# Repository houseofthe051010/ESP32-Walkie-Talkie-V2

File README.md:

# ESP32 Walkie Talkie V2

ESP32 Walkie Talkie V2 is a custom handheld digital voice-radio board. It combines an ESP32, a dedicated 915 MHz SX1262 radio, digital microphone, Class-D speaker amplifier, battery charging, battery monitoring, USB-C programming, controls, and an external OLED connection on one 45 × 100 mm PCB.

The goal is to build a pair of rechargeable handheld radios that can exchange compressed voice without depending on Wi-Fi, cellular service, or an internet connection. The separate sub-GHz radio provides the long-range link while the ESP32 handles audio capture, compression, controls, display updates, and packet management.

> [!IMPORTANT]
> **Current status: production-candidate PCB design, not a completed physical build.** The PCB has passed ERC/DRC and manufacturing-file validation, but the enclosure and application firmware are not finished and no assembled prototype has been bench-tested yet. See [Hack Club submission status](HACK_CLUB_SUBMISSION.md) before submitting this repository for funding.

## Why this project exists

The project started as an attempt to make a longer-range, customizable alternative to a Wi-Fi-only ESP32 intercom. Designing the complete board also made it possible to choose the controls, audio path, battery monitoring and enclosure geometry instead of stacking several development boards together. A major part of the design process became learning how electrical choices affect real small-run assembly cost, stock availability, mechanical fit and manufacturability.

## What it does

- Captures digital audio with an ICS-43432 I2S microphone.
- Uses the ESP32 to process and eventually compress voice audio.
- Sends packetized audio over an Ai-Thinker Ra-01SH/SX1262 915 MHz radio.
- Drives a 4–8 Ω speaker through a MAX98357A I2S Class-D amplifier.
- Displays channel, battery, and radio state on a hand-wired SSD1306 I2C OLED.
- Provides five buttons, a potentiometer input, status LED, charging LED, and battery-voltage monitoring.
- Charges a single-cell Li-ion/LiPo battery through USB-C.

The intended voice mode is SX1262 GFSK/FSK with a low-rate codec and packet-loss handling. Ordinary LoRa modulation is useful for low-rate telemetry, but it does not provide enough continuous bandwidth for normal real-time voice.

## Hardware

| Subsystem | Part | Purpose |
|---|---|---|
| Controller | ESP32-WROOM-32D-N16 | Audio processing, controls, display and packet handling |
| Long-range radio | Ai-Thinker Ra-01SH / SX1262 | 803–930 MHz radio with I-PEX/U.FL-compatible antenna socket |
| Microphone | ICS-43432 | Bottom-port I2S digital microphone |
| Speaker amplifier | MAX98357A | I2S Class-D differential speaker output |
| Power regulator | TPS63021 | Fixed 3.3 V synchronous buck-boost supply |
| Charger | TP4056 | Approximately 500 mA single-cell Li-ion charging |
| Battery protection | DW01A + FS8205A | Cell overcharge, overdischarge and fault protection |
| USB programming | CH340C | USB-to-UART with automatic boot/reset control |
| Display | External SSD1306 module | Four hand-wired I2C holes: `SDA`, `SCL`, `3V3`, `GND` |

## Design views

| PCB front | PCB back |
|---|---|
|  |  |

The KiCad board is exactly **45.000 × 100.000 mm**, uses **two copper layers**, and includes four 3.2 mm M3 mounting holes. The OLED is mounted above the main PCB on wires or spacers, and the enclosure-mounted 40 mm speaker sits over the upper component region with its Z-clearance checked during enclosure design.

The repository currently contains a PCB STEP export, shown above. A complete enclosure CAD assembly and enclosure source file are still required for a complete Hack Club design submission.

## How the system connects

```text
Li-ion cell -> charger/protection -> power switch -> 3.3 V buck-boost -> ESP32
                                                       |            |
                                                       |            +-> OLED / controls
                                                       +-> microphone / SX1262 radio

Li-ion switched rail -------------------------------------> MAX98357A -> speaker
USB-C -> charging
USB-C -> CH340C -> ESP32 programming UART
Ra-01SH I-PEX socket -> tuned 915 MHz antenna
```

The full circuit is documented by the editable [KiCad schematic](<Schematics/Final Draft/KiCad Project/walkiepcb.kicad_sch>). Off-board wiring and mechanical assembly are described in [ASSEMBLY.md](ASSEMBLY.md).

## Intended use

Once the firmware is implemented, a user will charge each handset through USB-C, attach the correct 915 MHz antenna, turn on the side power switch, select a channel with the controls, and hold the push-to-talk button while speaking. The receiving handset will decode the packets and play the voice through its speaker.

The main switch must be on for USB programming because the CH340C intentionally runs from switched 3.3 V. Charging remains available while the switch is off. Never transmit without an antenna, and use only frequencies and power levels permitted in the operating region.

## Building the project

1. Order the matched Gerber, BOM and corrected CPL files from `Schematics/Final Draft/Manufacturing/`.
2. In the assembler preview, confirm that the ESP32 antenna faces the left board edge and the Ra-01SH matches the supplied render.
3. Inspect and electrically bring up one board using the [first-power-up checklist](<Schematics/Final Draft/KiCad Project/FIRST_POWER_UP_CHECKLIST.md>).
4. Hand-solder the OLED, five buttons, potentiometer, speaker, battery, external LED and power switch according to [ASSEMBLY.md](ASSEMBLY.md).
5. Design and print/machine an enclosure that secures the PCB, speaker, battery, display, antenna cable and controls.
6. Flash and test the application firmware before installing the battery permanently.

The validated release files and exact upload instructions are in [Schematics/Final Draft](<Schematics/Final Draft>). Machine validation for that release reports **ERC 0 errors/0 warnings, DRC 0 violations/0 unconnected pads, and 64/64 BOM/CPL reference parity**.

## Repository map

- [`Schematics/Final Draft`](<Schematics/Final Draft>) — order-candidate KiCad source, Gerbers, BOM, corrected CPL, renders and audit reports
- [`Schematics/KiCad Project`](<Schematics/KiCad Project>) — editable working KiCad project and engineering notes
- [`CAD`](CAD) — PCB STEP export; enclosure CAD is still pending
- [`Firmware`](Firmware) — firmware status and planned architecture
- [`DESIGN_JOURNAL.md`](DESIGN_JOURNAL.md) — dated Hack Club-style build journal
- [`docs/ENGINEERING_HISTORY.md`](docs/ENGINEERING_HISTORY.md) — detailed engineering decisions, mistakes and corrections
- [`BOM.csv`](BOM.csv) — root project-level funding BOM
- [`ASSEMBLY.md`](ASSEMBLY.md) — off-board wiring and build plan
- [`HACK_CLUB_SUBMISSION.md`](HACK_CLUB_SUBMISSION.md) — submission checklist and known blockers

## Project BOM

This budget builds a **pair of handsets** so that the radio link can be tested. Prices are planning estimates in USD and exclude shipping/tax. The PCBA line covers the two-board assembled prototype order; the [engineering BOM](<Schematics/Final Draft/KiCad Project/walkiepcb_bom_full.csv>) lists every installed component and JLC/LCSC number.

| Item | Qty | Est. unit | Est. total | Source / part |
|---|---:|---:|---:|---|
| Two assembled PCBs plus fabrication minimum | 1 lot | $105.00 | $105.00 | [JLCPCB](https://jlcpcb.com/); use the files in `Schematics/Final Draft/Manufacturing/` |
| 0.96-inch SSD1306 I2C OLED | 2 | $8.00 | $16.00 | [Waveshare 0.96-inch OLED (B)](https://www.waveshare.com/0.96inch-oled-b.htm) |
| 40 mm, 4–8 Ω speaker | 2 | $2.00 | $4.00 | [Adafruit 4 Ω 3 W speaker](https://www.adafruit.com/product/3968) or equivalent |
| Protected 1S LiPo battery | 2 | $12.50 | $25.00 | [Adafruit 2000 mAh LiPo](https://www.adafruit.com/product/2011) or enclosure-compatible protected cell |
| 868/915 MHz flexible antenna with I-PEX/U.FL | 2 | $8.00 | $16.00 | Taoglas `FXP75.07.0100A` or equivalent 50 Ω antenna |
| 6 × 6 mm two-pin tactile buttons | 10 | $0.25 | $2.50 | `TL1100F100QG` or footprint-compatible equivalent |
| 10 kΩ linear potentiometer | 2 | $1.00 | $2.00 | Generic panel-mount B10K potentiometer |
| SPST power switch | 2 | $1.00 | $2.00 | Generic panel-mount switch rated above 2 A DC |
| 5 mm external LED | 2 | $0.10 | $0.20 | Generic LED; board includes a 330 Ω resistor |
| Wire, heat-shrink and mounting hardware | 1 lot | $5.00 | $5.00 | Generic hookup materials and M3 hardware |
| Enclosure material | 2 | TBD | TBD | Pending complete enclosure CAD |
| **Estimated subtotal before enclosure/shipping/tax** |  |  | **$177.70** |  |

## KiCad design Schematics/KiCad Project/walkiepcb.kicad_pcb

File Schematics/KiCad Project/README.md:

# Walkie-talkie PCB

This project is a two-layer, 45 × 100 mm handheld voice-radio PCB built around an ESP32-WROOM-32D-N16, an Ai-Thinker Ra-01SH/SX1262 915 MHz radio with I-PEX antenna socket, an ICS-43432 digital microphone, and a MAX98357A Class-D speaker amplifier.

The current design is the **Final Draft (2026-08-27)** of the Revision E WROOM + CH340C + Ra-01SH board. The exact pre-audit Revision E state is preserved in `../Legacy/Revision E pre-final audit 2026-08-27/`. An S3 radio-board variant was discussed but intentionally not built yet.

## Current features

- ESP32-WROOM-32D-N16 with 16 MB flash and onboard 2.4 GHz PCB antenna.
- Ra-01SH / SX1262 803–930 MHz radio, intended for 915 MHz operation, with on-module I-PEX/U.FL-compatible connector.
- CH340C USB-UART with DTR/RTS automatic programming.
- USB-C charging/programming port centered at the bottom.
- TP4056 charger set for approximately 500 mA.
- TPS63021 fixed 3.3 V synchronous buck-boost, allowing regulated operation as a 1S Li-ion cell moves above and below 3.3 V.
- Raw-battery ADC on GPIO34 using a 100 kΩ/100 kΩ divider and 100 nF filter.
- ICS-43432 bottom-port I2S microphone.
- MAX98357A I2S Class-D amplifier powered from `SYS_SW`.
- Four-hole wired interface for a commercial SSD1306 I2C OLED; no soldered bare OLED panel or header model.
- Five hand-soldered buttons: symmetric 2×2 cluster plus isolated BTN5.
- Top-left potentiometer and external LED wiring holes.
- Basic red charging and status LEDs near USB-C.
- Four M3 mounting holes, one in each cleared corner.
- Probe/expansion pads for 3V3, GND, UART TX/RX, EN, GPIO0, LED_STATUS/GPIO2, and GPIO12.
- DW01A + FS8205A cell protection, USB ESD protection, and resettable system fuse retained.
- Final-audit corrections: CH340C uses switched 3V3 logic, and R26 provides the ICS-43432's recommended 100 kΩ SD pull-down.

Real-time voice firmware should use compressed, packetized audio over SX1262 GFSK/FSK. LoRa mode is useful for low-rate, long-range data but is not suitable for ordinary continuous voice bandwidth.

## Design journal

### Initial design

The project began as a compact ESP32 walkie-talkie with USB-C charging/programming, a directly soldered OLED, I2S microphone and speaker amplifier, five controls, Li-ion charging/protection, and a regulated logic rail. The original narrow-board target was about 35 mm.

### Mechanical resize and speaker clarification

The enclosure target changed to approximately 100 mm tall × 45 mm wide. The wider board was used to improve button ergonomics, microphone separation, current routing, USB routing, and RF clearance. A 40 mm speaker occupies the upper enclosure region, but the speaker is mounted above the PCB. Therefore short components and RF/power circuitry are allowed underneath its X/Y projection as long as enclosure Z-clearance is verified. The OLED reference still obeys the hard rule that its top must be at least 47.5 mm below the PCB top; the final reference top is Y = 50.0 mm.

### Power-supply redesign

The AP7361C 3.2 V LDO was removed because a linear regulator would fall out of regulation while a 1S cell still had useful energy. It was replaced with a fixed 3.3 V TPS63021 synchronous buck-boost using the manufacturer's inductor/capacitor arrangement. MAX98357A stayed on the raw switched rail.

### Cost and assembly review

JLC's two-board price was much higher than the sum of retail component prices because setup, stencil, Extended-line feeder fees, and difficult packages dominate very small runs. The bare OLED was also overpriced and sometimes unavailable. The design changed to four bare 2.54 mm holes for a separately purchased SSD1306 I2C OLED module.

Several safety parts were examined as cost-down candidates: the resettable fuse, USB ESD device, DW01A, and FS8205A. They remain in Revision D because they provide fault, transient, overcharge, and overdischarge protection. A deliberately unprotected variant was not released.

### ESP32 and long-range radio decision

An ESP32-S3 with native USB was considered, including a separate S3 version. Economy/standard classification made the small-run price unattractive. The current board instead uses the Economic-compatible ESP32-WROOM-32D-N16 plus CH340C.

The ESP32 no longer needs an external antenna connector. A separate Ra-01SH/SX1262 915 MHz module supplies the long-range link and the I-PEX connector. The radio is near the top edge for coax access. The ESP32 moved downward into the previously empty middle area beneath the elevated OLED, with its PCB antenna facing the left board edge.

### Control and indicator revision

The OLED connector moved upward by 5 mm and was changed to a custom holes-only footprint. The four-button cluster was expanded to 12.5 mm pitch, BTN5 stayed isolated, and the microphone moved directly above BTN5. The POT and external LED holes moved to the top-left. Basic C2286 red LEDs were added for charge and status indication near USB-C.

### Final routing and verification

The board was routed as two layers with 0.40 mm high-current trunks, 0.30 mm 3V3 routing, short package neck-downs, and a B.Cu ground plane. The final difficult connections were the right-edge USB power path and the Class-D negative output. The switch connector pads were normalized to 3.0 mm around 1.5 mm drills so a short 0.20 mm USB edge neck could maintain clearance. The amplifier ground was explicitly carried into the main ground network.

Final machine checks on 2026-08-27:

- ERC: 0 errors, 0 warnings.
- DRC: 0 violations.
- Unconnected pads: 0.
- Board: 45 × 100 mm, two copper layers.

### Revision E mounting, OLED, and expansion update

Four M3 mounting holes were added at the corners, the Ra-01SH moved inward while retaining top-edge coax access, and the high-current wire pads were reduced to 2.6 mm copper around 1.2 mm drills to free mechanical space. The OLED holes were rotated 180° so their physical left-to-right order is `SDA`, `SCL`, `3V3`, `GND`, placing ground on the right. Two nearby DNP probe pads expose the status-LED net (GPIO2) and GPIO12 for optional future hardware. GPIO12 remains a boot-strapping pin and must not be forced to an invalid level during reset.

The Final Draft was machine checked on 2026-08-27: ERC 0 errors and 0 warnings, DRC 0 violations, and 0 unconnected pads.

The hand-soldered connector holes were subsequently labeled on `B.Silkscreen`. The labels identify the potentiometer, external LED, battery, speaker, OLED, and system-switch pads while leaving the component-side layout uncluttered. Copper traces underneath do not interfere because the solder mask separates copper from the silkscreen ink.

Back-side branding was added in the open upper-center region: large italic `Verma Industries` lettering with `ESP32 Walkie Talkie V2` beneath it. The artwork uses ordinary white silkscreen and therefore remains compatible with a black solder-mask order.

The expanded mistakes, failed approaches, fixes, and remaining physical-validation tasks are maintained in the repository-level [`DESIGN_JOURNAL.md`](../../DESIGN_JOURNAL.md). That document is the canonical project history; this file remains the compact hardware overview stored beside the KiCad source.

## Key files

- `walkiepcb.kicad_sch` — current schematic.
- `walkiepcb.kicad_pcb` — current routed PCB.
- `walkiepcb_jlc_bom.csv` — four-column, upload-ready JLC BOM with DNP parts excluded.
- `walkiepcb_bom_full.csv` — engineering BOM with fields for installed and hand-soldered parts.
- `PIN_ASSIGNMENTS.md` — firmware pin map.
- `LAYOUT_NOTES.md` — enclosure coordinates and routing notes.
- `JLC_PART_RESEARCH.md` — part selection and current Economic/stock evidence.
- `JLC_COST_ESTIMATE.md` — small-run cost explanation and planning range.
- `ERC_NOTES.md` — electrical verification record.
- `ORDER_READINESS_REPORT.md` — final pre-production audit, known risks, and uploader checks.
- `ASSEMBLY_ORIENTATION_CHECK.md` — required human verification of U6/U8 and other critical rotations.
- `FIRST_POWER_UP_CHECKLIST.md` — current-limited prototype bring-up sequence.
- `legacy/revision_c_s3_2026-08-24/` — preserved earlier design.

## Before ordering

Upload the Gerber ZIP, BOM, and **corrected JLC CPL** from `../Final Draft/Manufacturing/` together. Never upload the raw KiCad position CSV as the CPL. In JLC's preview, U6's PCB antenna must face the left edge and U8 must match the supplied top render, with its I-PEX connector on the module's board-interior/lower side. Recheck every Extended row for live stock and exact package match, especially the ICS-43432, TPS63021, CH340C, ESP32-WROOM, MAX98357A, and Ra-01SH.

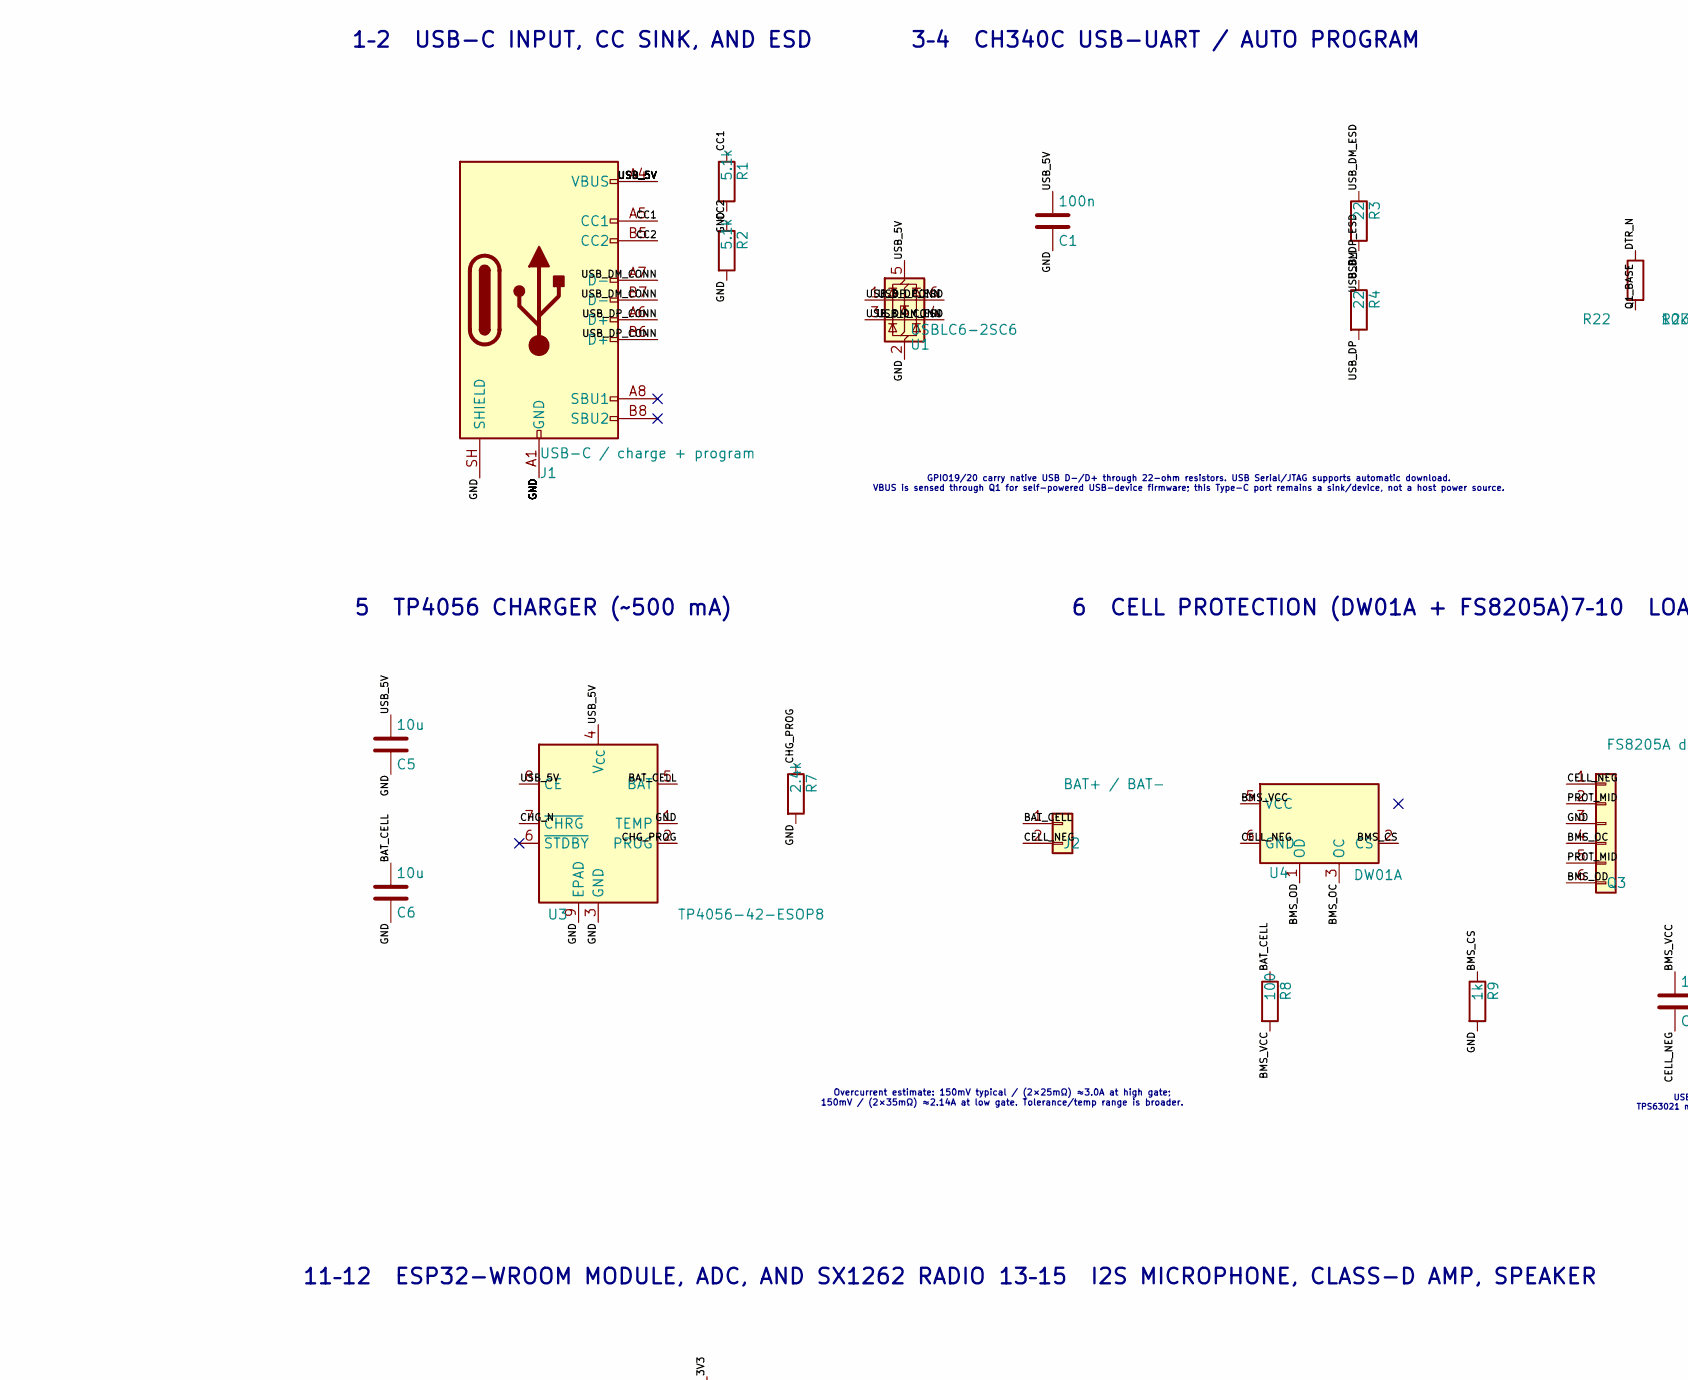
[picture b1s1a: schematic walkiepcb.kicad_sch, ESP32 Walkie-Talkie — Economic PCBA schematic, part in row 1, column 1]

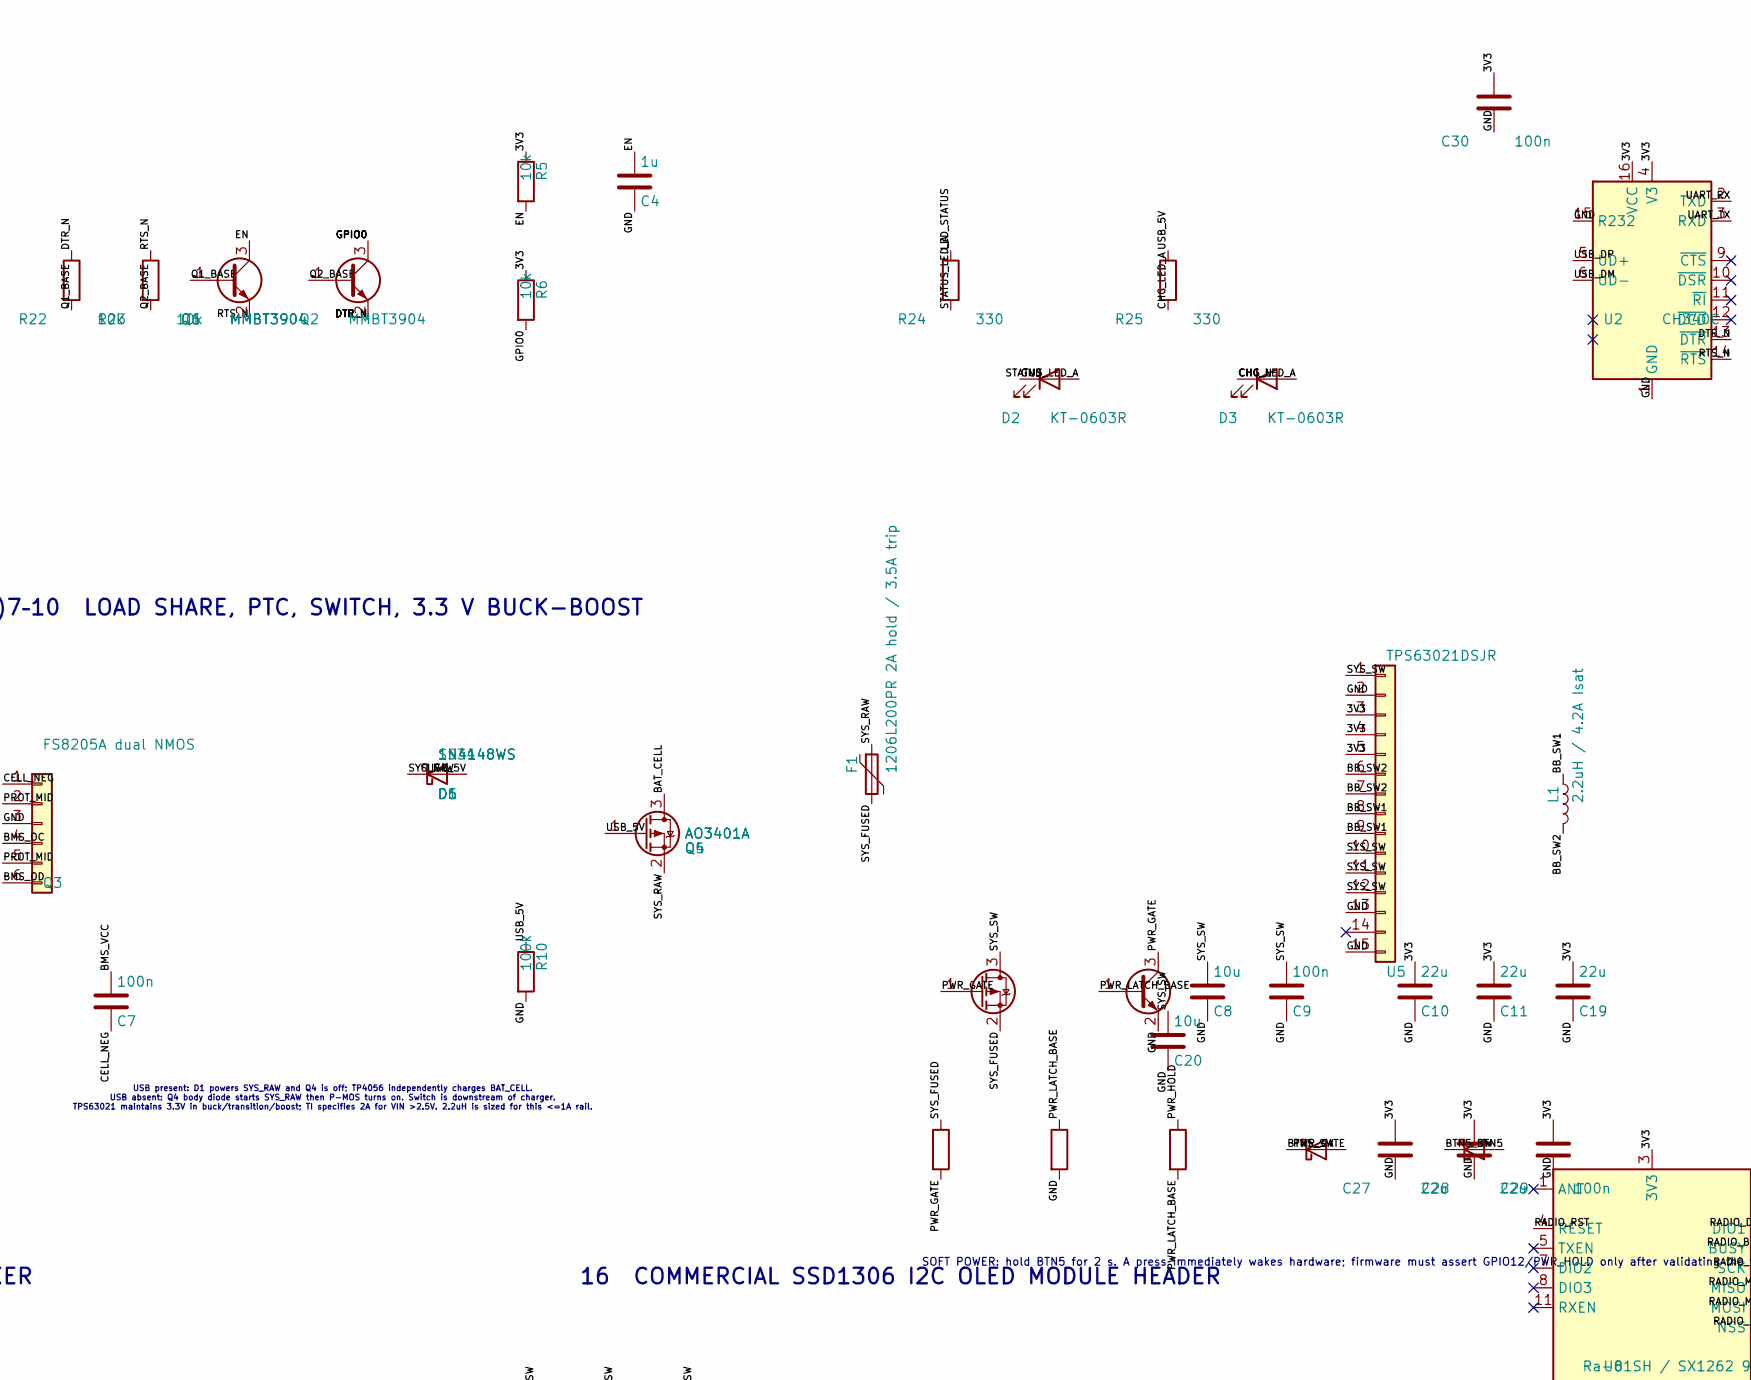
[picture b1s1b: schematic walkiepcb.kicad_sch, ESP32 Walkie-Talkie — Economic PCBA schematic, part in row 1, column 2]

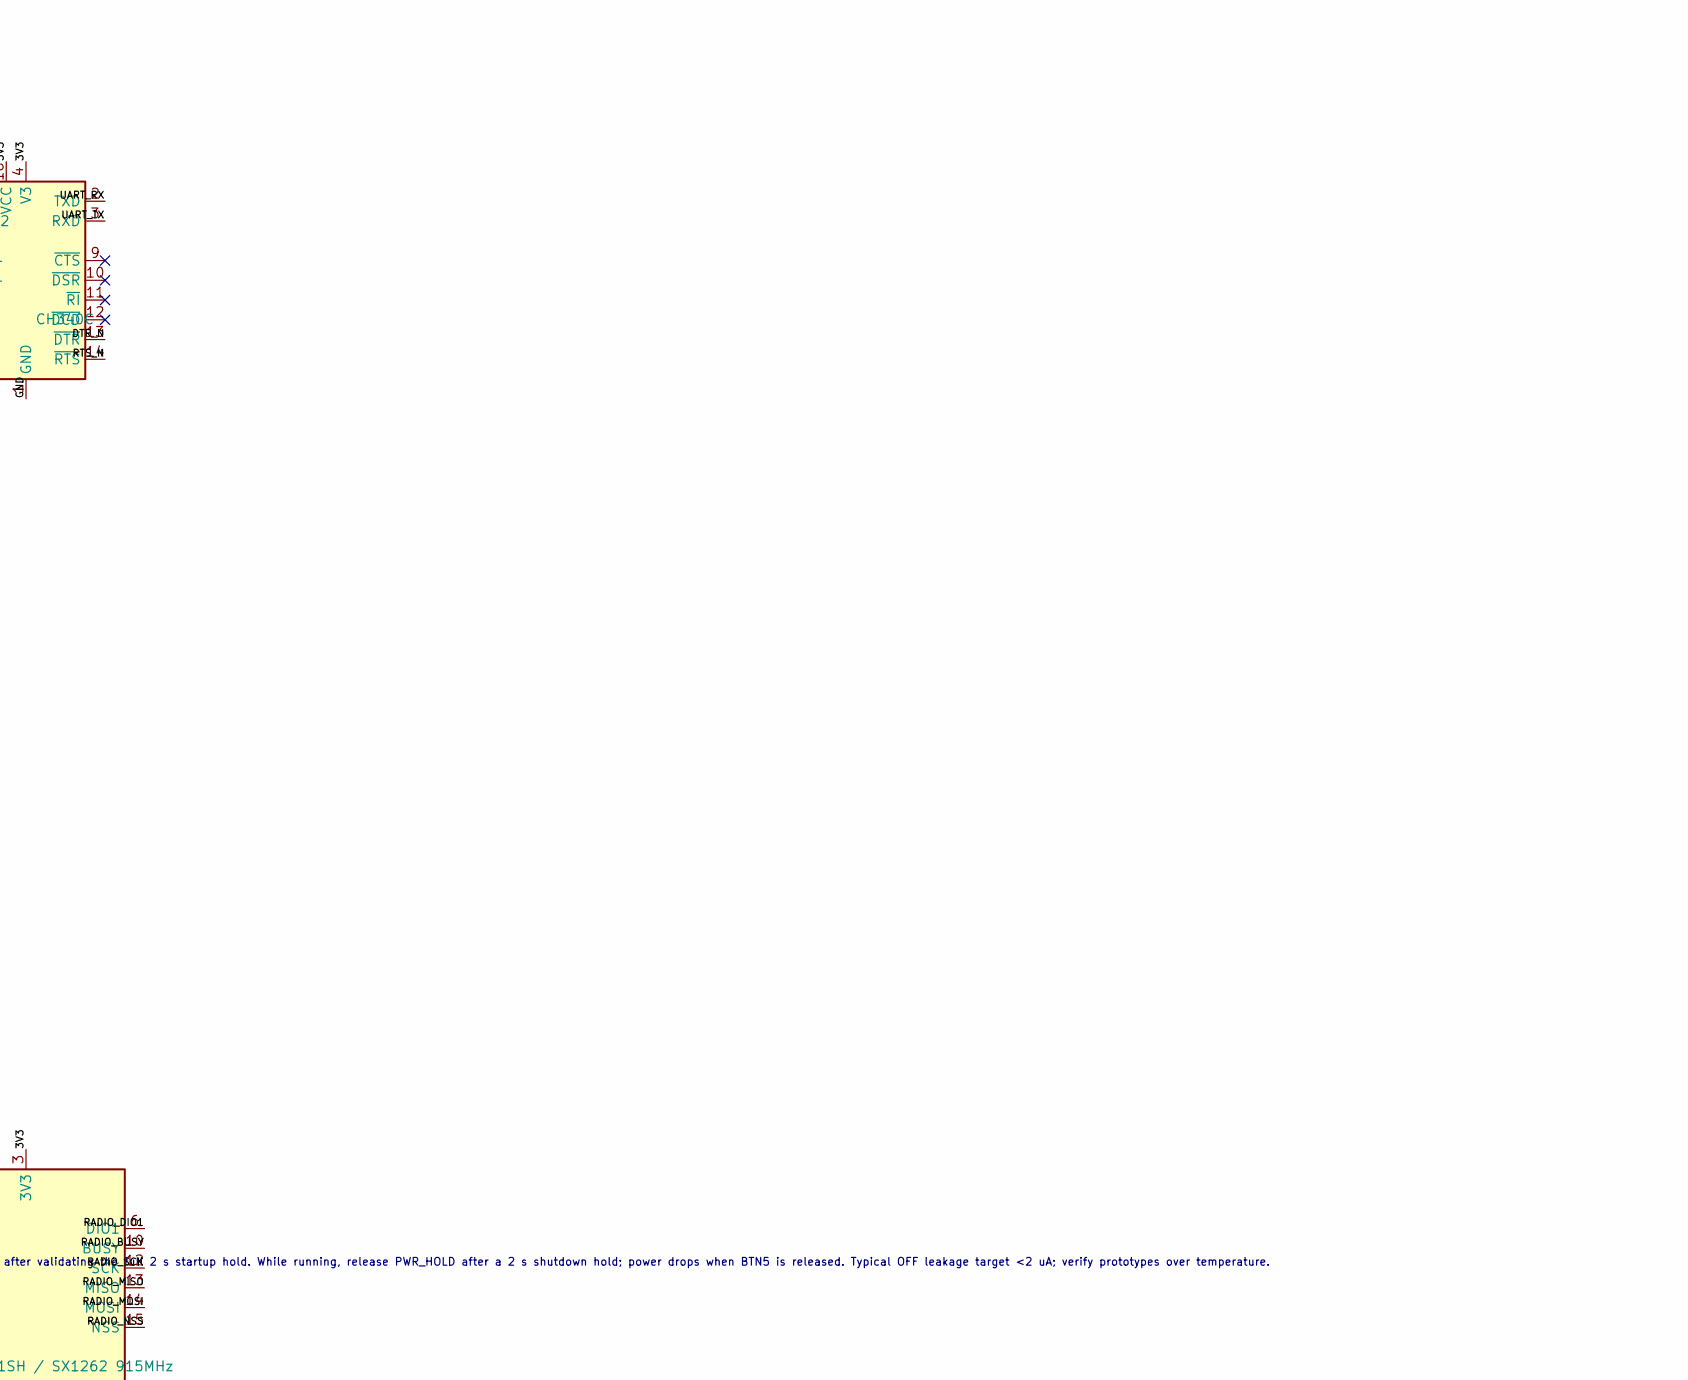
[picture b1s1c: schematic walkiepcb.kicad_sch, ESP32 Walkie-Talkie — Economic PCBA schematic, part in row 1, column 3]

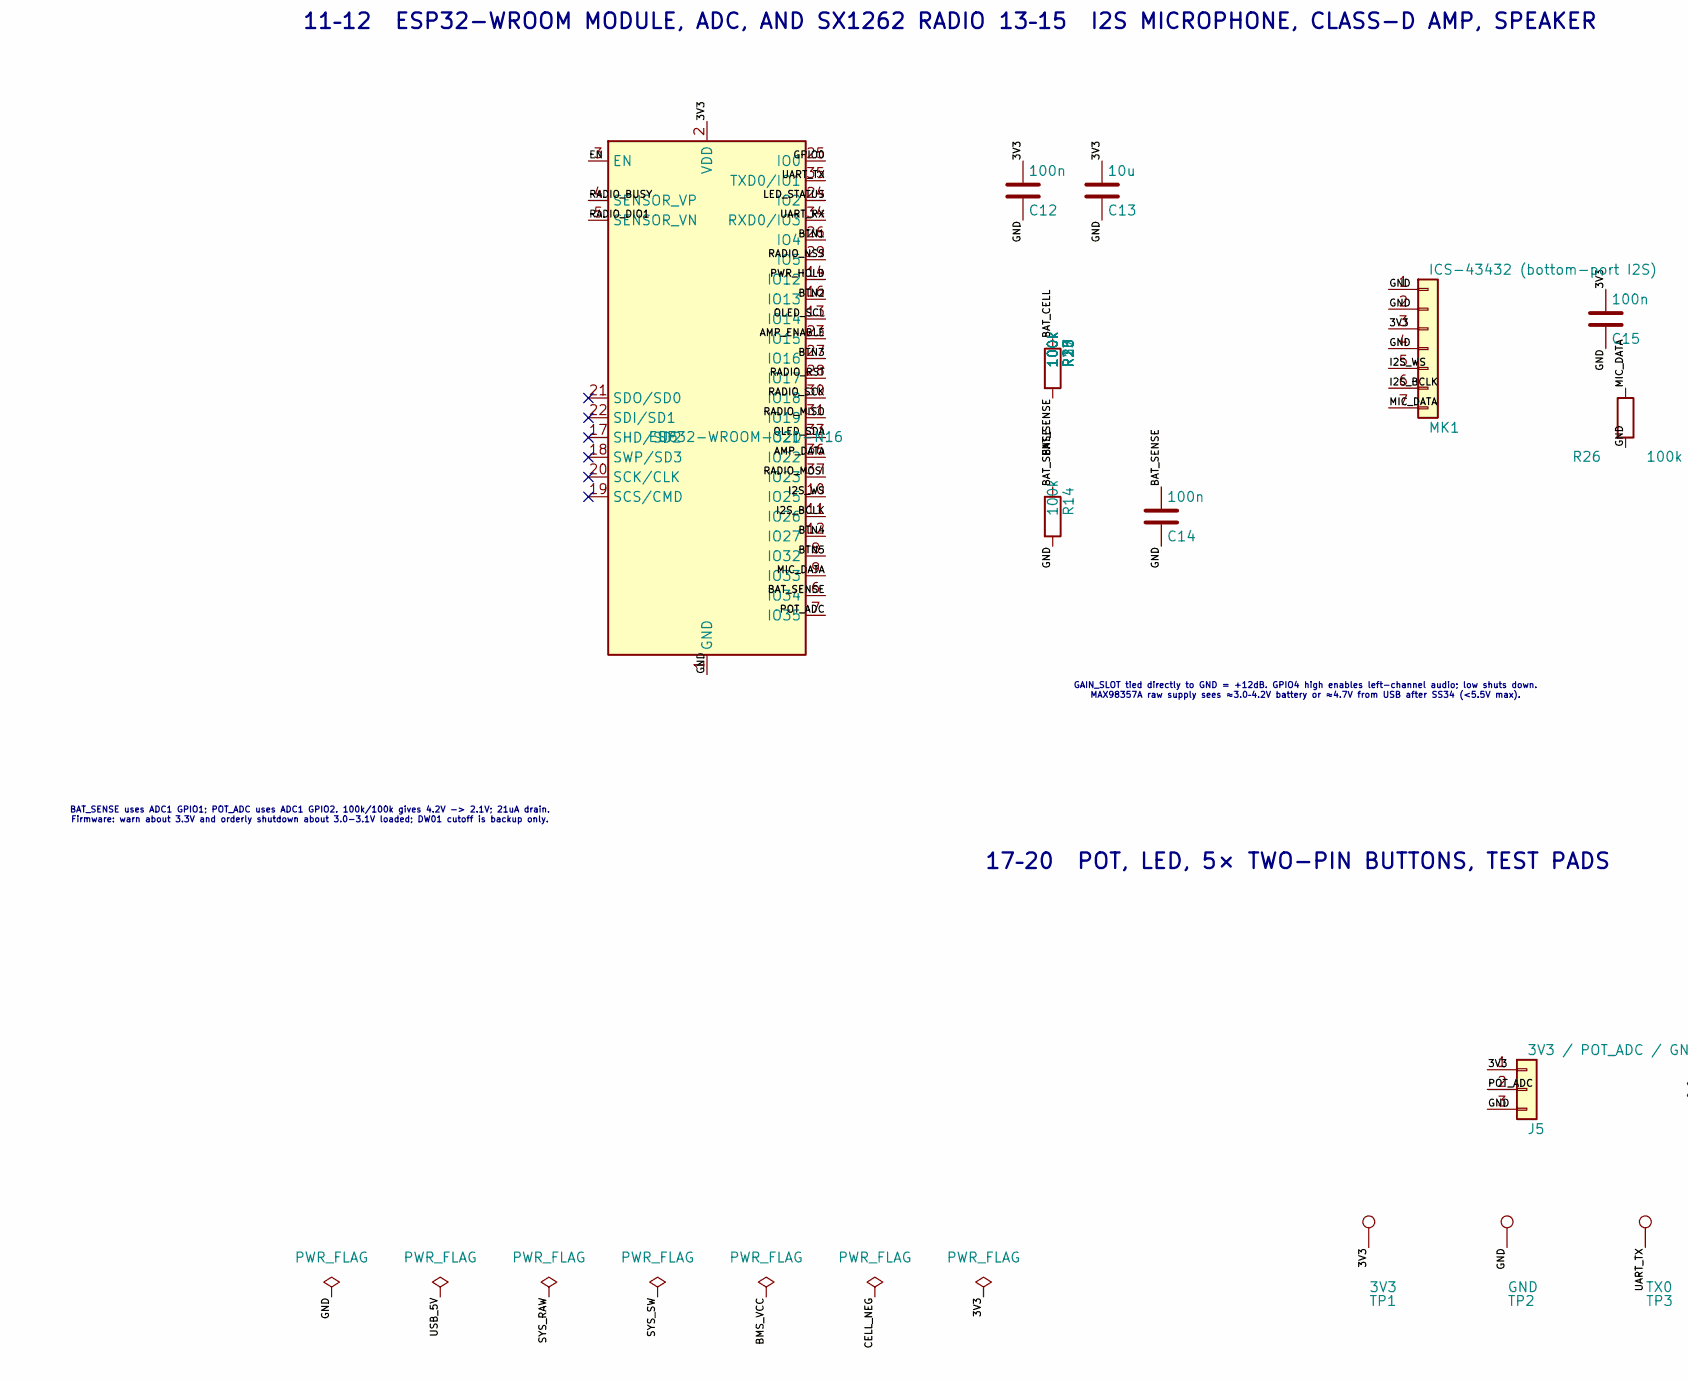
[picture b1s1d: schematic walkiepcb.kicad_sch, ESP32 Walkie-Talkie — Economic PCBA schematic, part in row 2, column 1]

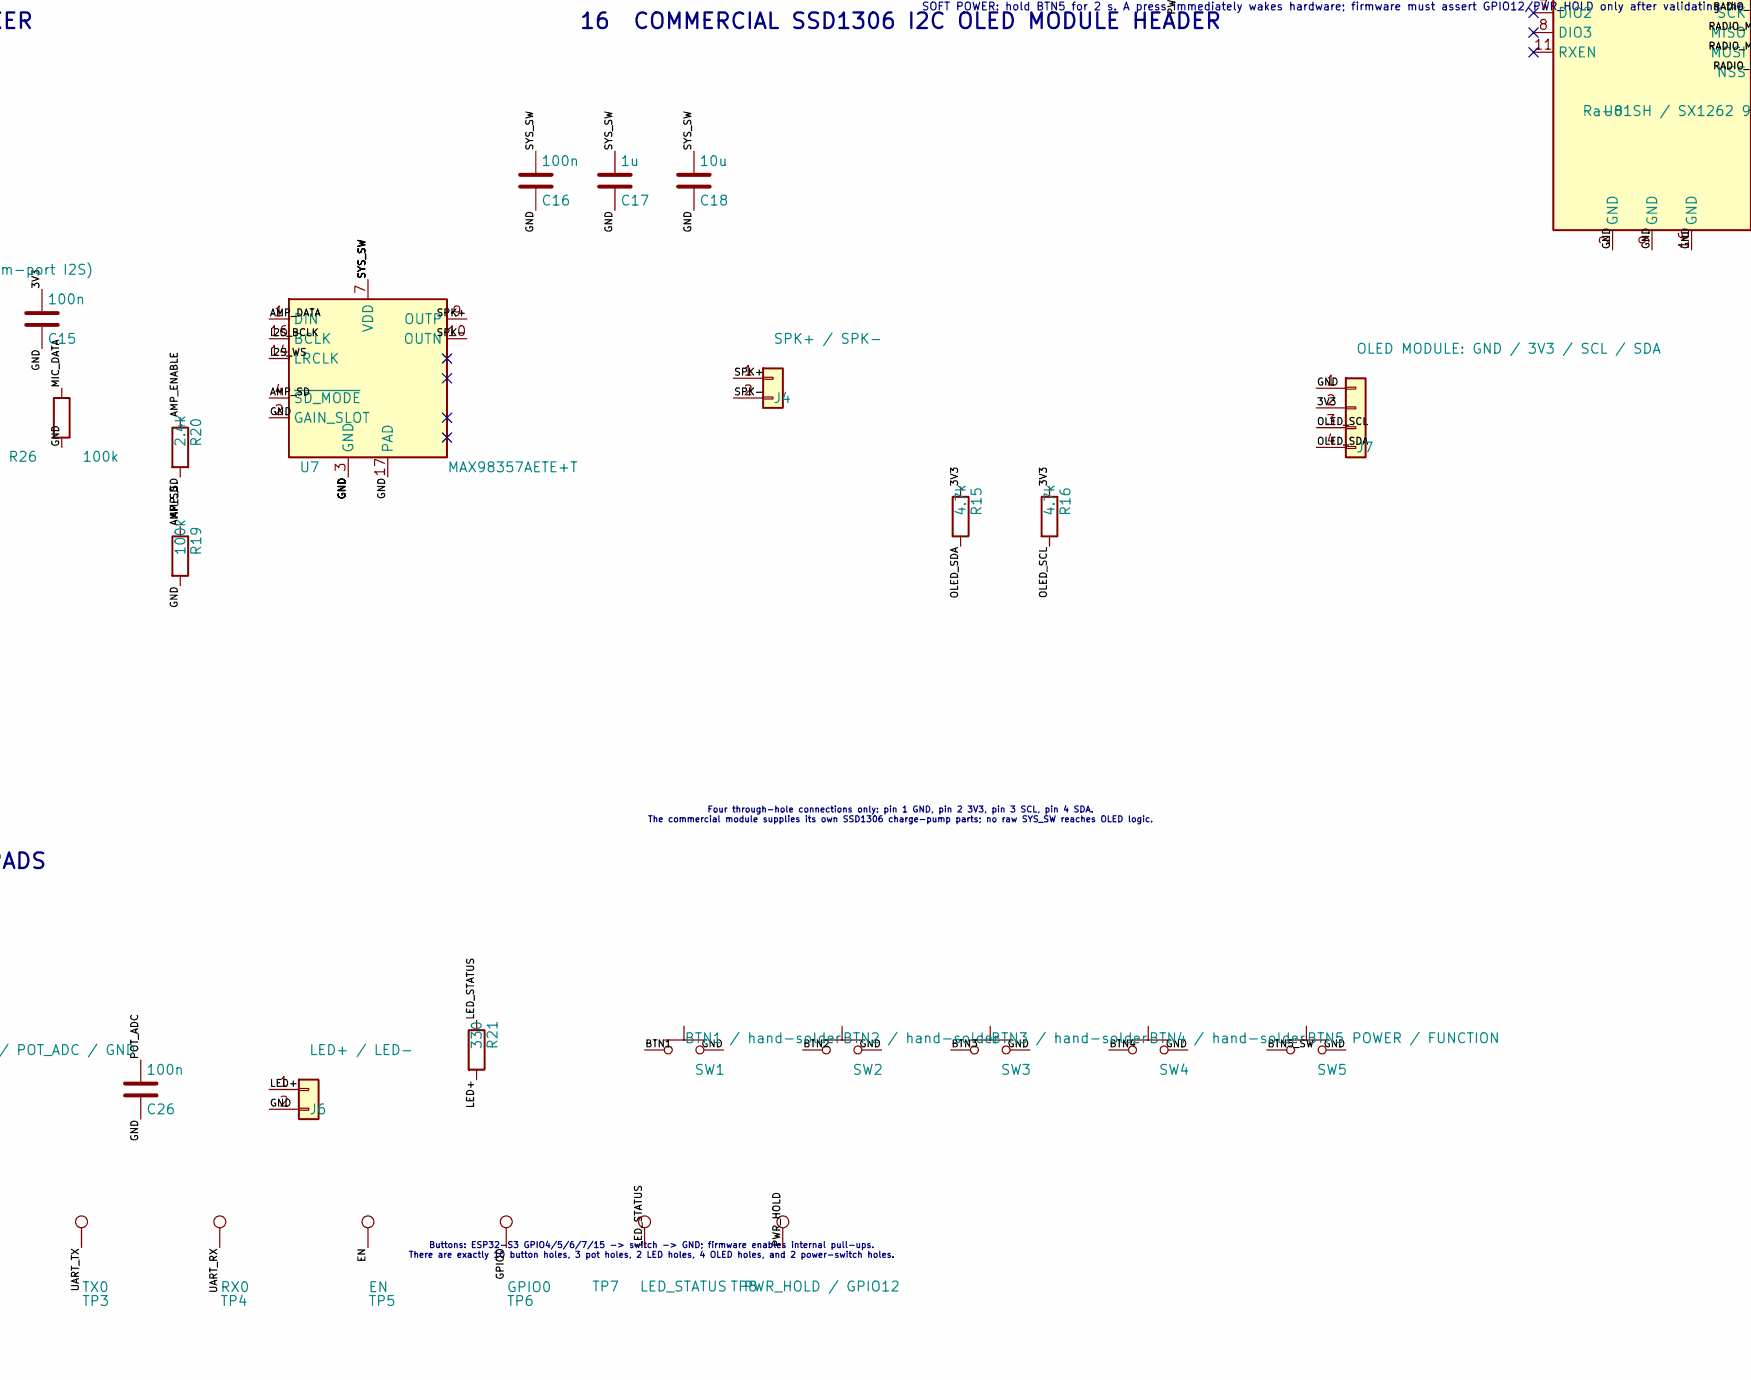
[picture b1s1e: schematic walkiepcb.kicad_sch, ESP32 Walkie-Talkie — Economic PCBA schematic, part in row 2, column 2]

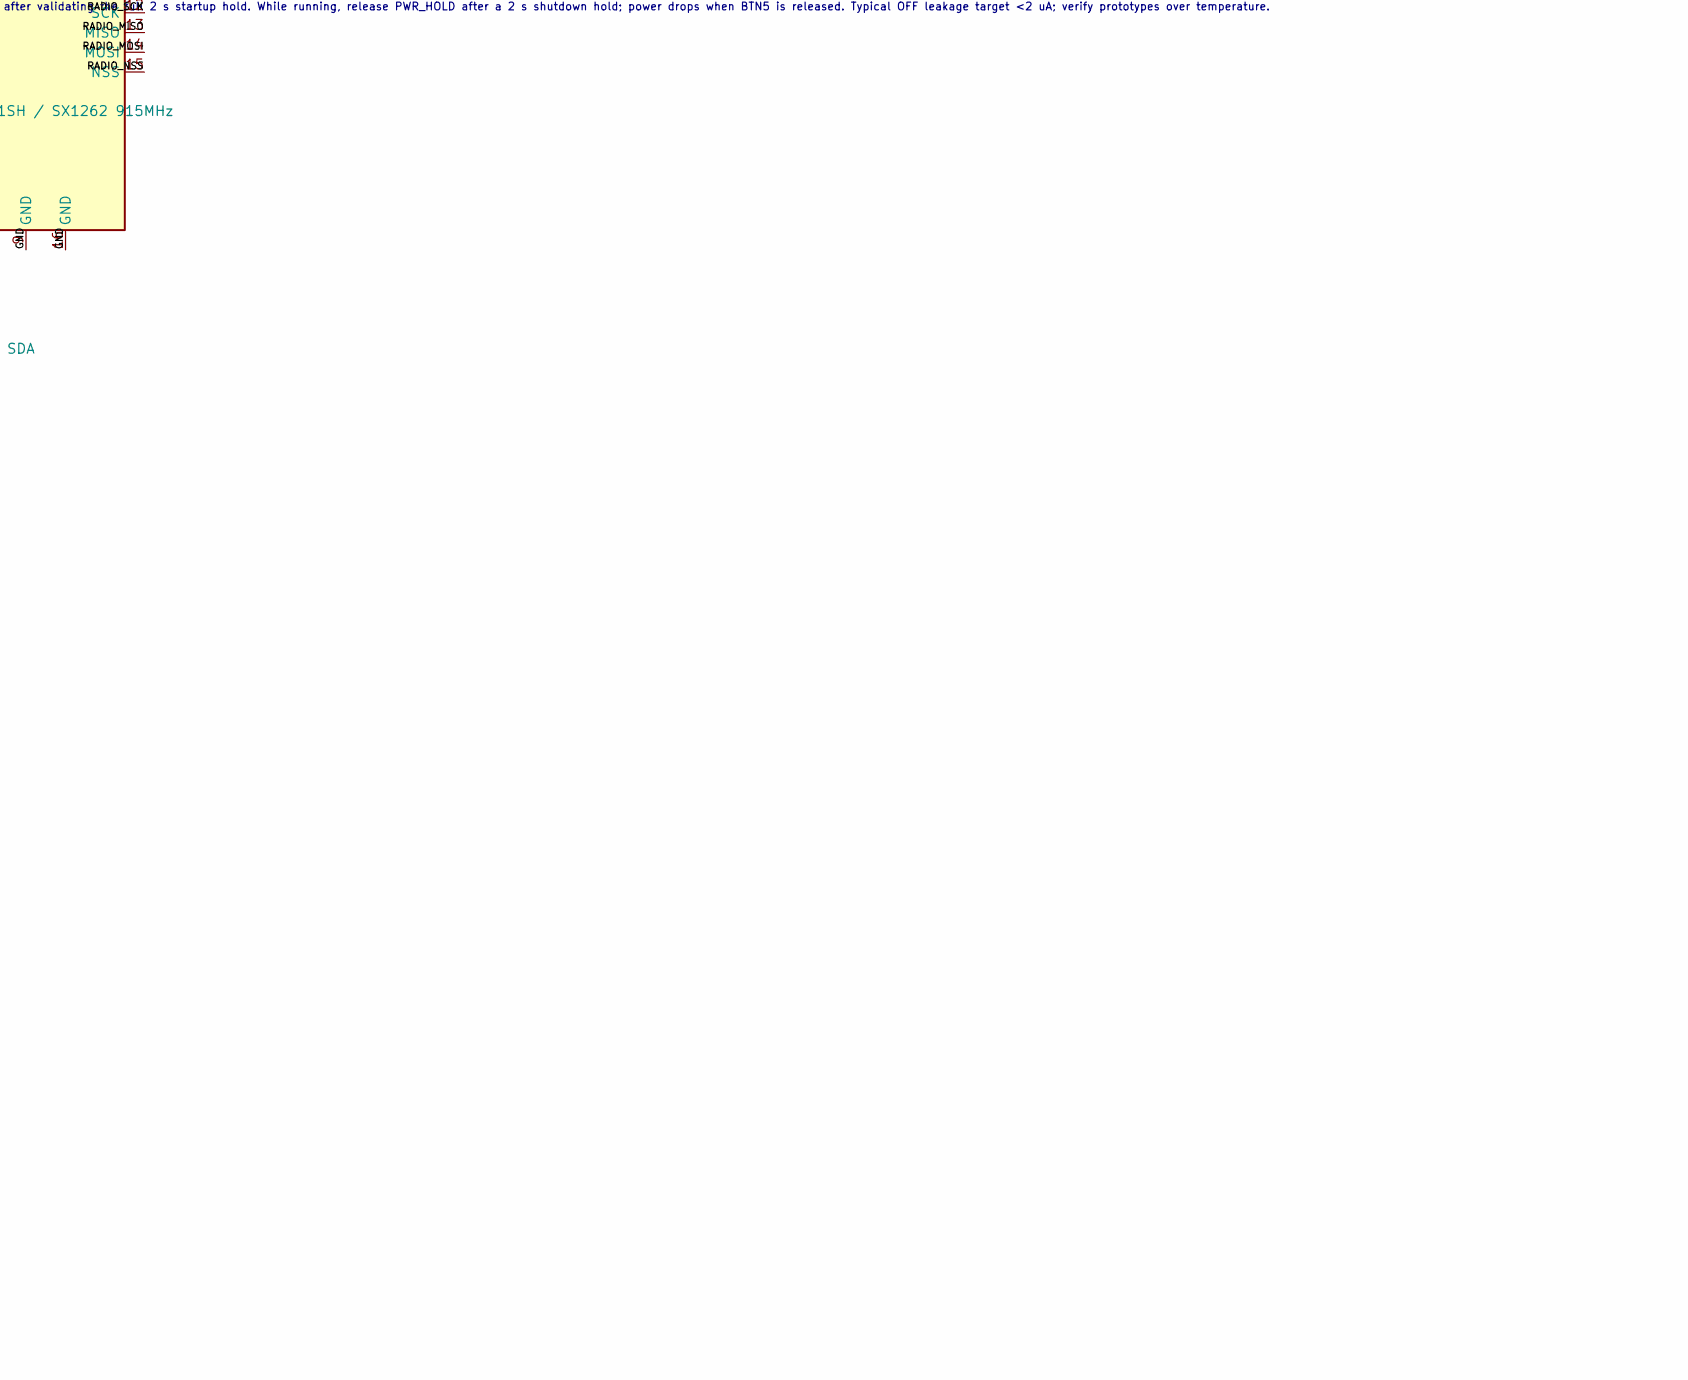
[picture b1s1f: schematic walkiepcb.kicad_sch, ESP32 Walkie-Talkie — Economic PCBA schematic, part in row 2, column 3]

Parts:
C1, C7, C9, C12, C14, C15, C16, C26, C29, C30: 100n; C_0603_1608Metric; MPN CC0603KRX7R9BB104; JLC/LCSC C14663
C4, C17: 1u; C_0603_1608Metric; MPN CL10A105KB8NNNC; JLC/LCSC C15849
C5, C6, C8, C13, C18, C20: 10u; C_0805_2012Metric; MPN CL21A106KAYNNNE; JLC/LCSC C15850
C10, C11, C19, C27, C28: 22u; C_0805_2012Metric; MPN CL21A226MAQNNNE; JLC/LCSC C45783
D1: SS34; D_SMA; MPN SS34; JLC/LCSC C8678
D2, D3: KT-0603R; LED_0603_1608Metric; MPN KT-0603R; JLC/LCSC C2286
D5, D6: 1N4148WS; D_SOD-323; MPN 1N4148WS; JLC/LCSC C2128
F1: 1206L200PR 2A hold / 3.5A trip; Fuse_1206_3216Metric; MPN 1206L200PR; JLC/LCSC C151163
J1: USB-C / charge + program; USB_C_Receptacle_HRO_TYPE-C-31-M-12; MPN TYPE-C-31-M-12; JLC/LCSC C165948
J2: BAT+ / BAT-; WirePads_2_P5.08mm; MPN 2 solder pads; JLC Classification DNP
J4: SPK+ / SPK-; WirePads_2_P5.08mm; MPN 2 solder pads; JLC Classification DNP
J5: 3V3 / POT_ADC / GND; WirePads_3_P2.54mm; MPN 3 solder pads; JLC Classification DNP
J6: LED+ / LED-; WirePads_2_P2.54mm; MPN 2 solder pads; JLC Classification DNP
J7: OLED MODULE: GND / 3V3 / SCL / SDA; OLED_1x04_P2.54mm_HolesOnly; MPN 2.54mm 1x4 header; JLC Classification DNP
L1: 2.2uH / 4.2A Isat; L_Murata_DFE201610P; MPN MWTC201610S2R2MT; JLC/LCSC C6807735
MK1: ICS-43432 (bottom-port I2S); ICS-43432_LGA7_4x3mm; MPN ICS-43432; JLC/LCSC C574021
Q1, Q2, Q6: MMBT3904; SOT-23; MPN MMBT3904; JLC/LCSC C20526
Q3: FS8205A dual NMOS; SOT-23-6; MPN FS8205A; JLC/LCSC C908265
Q4, Q5: AO3401A; SOT-23; MPN AO3401A; JLC/LCSC C15127
R1, R2: 5.1k; R_0603_1608Metric; MPN 0603WAF5101T5E; JLC/LCSC C23186
R3, R4: 22; R_0603_1608Metric; MPN 0603WAF220JT5E; JLC/LCSC C23345
R5, R6, R22, R23: 10k; R_0603_1608Metric; MPN 0603WAF1002T5E; JLC/LCSC C25804
R7, R20: 2.4k; R_0603_1608Metric; MPN 0603WAF2401T5E; JLC/LCSC C22940
R8: 100; R_0603_1608Metric; MPN 0603WAF1000T5E; JLC/LCSC C22775
R9: 1k; R_0603_1608Metric; MPN 0603WAF1001T5E; JLC/LCSC C21190
R10, R13, R14, R19: 100k; R_0603_1608Metric; MPN 0603WAF1003T5E; JLC/LCSC C25803
R15, R16: 4.7k; R_0603_1608Metric; MPN 0603WAF4701T5E; JLC/LCSC C23162
R21, R24, R25: 330; R_0603_1608Metric; MPN 0603WAF3300T5E; JLC/LCSC C23138
R26, R27, R28, R30: 100k; R_0402_1005Metric; MPN 0402WGF1003TCE; JLC/LCSC C25741
SW1: BTN1 / hand-solder; SW_Tactile_2Pin_6x6mm_P5.0mm; MPN TL1100F100QG; JLC Classification DNP
SW2: BTN2 / hand-solder; SW_Tactile_2Pin_6x6mm_P5.0mm; MPN TL1100F100QG; JLC Classification DNP
SW3: BTN3 / hand-solder; SW_Tactile_2Pin_6x6mm_P5.0mm; MPN TL1100F100QG; JLC Classification DNP
SW4: BTN4 / hand-solder; SW_Tactile_2Pin_6x6mm_P5.0mm; MPN TL1100F100QG; JLC Classification DNP
SW5: BTN5 POWER / FUNCTION; SW_Tactile_2Pin_6x6mm_P5.0mm; MPN TL1100F100QG; JLC Classification DNP
TP1: 3V3; TestPad_1.0mm; MPN SMD test pad; JLC Classification PCB
TP2: GND; TestPad_1.0mm; MPN SMD test pad; JLC Classification PCB
TP3: TX0; TestPad_1.0mm; MPN SMD test pad; JLC Classification PCB
TP4: RX0; TestPad_1.0mm; MPN SMD test pad; JLC Classification PCB
TP5: EN; TestPad_1.0mm; MPN SMD test pad; JLC Classification PCB
TP6: GPIO0; TestPad_1.0mm; MPN SMD test pad; JLC Classification PCB
TP7: LED_STATUS; TestPad_1.0mm; MPN SMD test pad; JLC Classification PCB
TP8: PWR_HOLD / GPIO12; TestPad_1.0mm; MPN SMD test pad; JLC Classification PCB
U1: USBLC6-2SC6; SOT-23-6; MPN USBLC6-2SC6; JLC/LCSC C7519
U2: CH340C; SOIC-16_3.9x9.9mm_P1.27mm; MPN CH340C; JLC/LCSC C7464026
U3: TP4056-42-ESOP8; SOIC-8-1EP_3.9x4.9mm_P1.27mm_EP2.41x3.3mm; MPN TP4056-42-ESOP8; JLC/LCSC C16581
U4: DW01A; SOT-23-6; MPN DW01A; JLC/LCSC C351410
U5: TPS63021DSJR; DFN-14-1EP_3x4mm_P0.5mm_EP1.7x3.3mm; MPN TPS63021DSJR; JLC/LCSC C202140
U6: ESP32-WROOM-32D-N16; ESP32-WROOM-32; MPN ESP32-WROOM-32D-N16; JLC/LCSC C529578
U7: MAX98357AETE+T; TQFN-16-1EP_3x3mm_P0.5mm_EP1.23x1.23mm; MPN MAX98357AETE+T; JLC/LCSC C910544
U8: Ra-01SH / SX1262 915MHz; Ai-Thinker_Ra-01SH; MPN Ra-01SH; JLC/LCSC C2764087

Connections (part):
/3V3: C10.1, C11.1, C12.1, C13.1, C15.1, C19.1, C27.1, C28.1, C29.1, C30.1, J5.1, J7.2, MK1.3, R5.1, R6.1, R15.1, R16.1, TP1.1, U2.4 (V3), U2.16 (VCC), U5.3, U5.4, U5.5, U6.2 (VDD), U8.3 (3V3)
/AMP_DATA: U6.36 (IO22), U7.1 (DIN)
/AMP_ENABLE: R20.1, U6.23 (IO15)
/AMP_SD: R19.1, R20.2, U7.4 (~SD_MODE)
/BAT_CELL: C6.1, J2.1, Q4.3 (D), R8.1, R13.1, U3.5 (BAT)
/BAT_SENSE: C14.1, R13.2, R14.1, U6.6 (IO34)
/BB_SW1: L1.1, U5.8, U5.9
/BB_SW2: L1.2, U5.6, U5.7
/BMS_CS: R9.1, U4.2 (CS)
/BMS_OC: Q3.4, U4.3 (OC)
/BMS_OD: Q3.6, U4.1 (OD)
/BMS_VCC: C7.1, R8.2, U4.5 (VCC)
/BTN1: SW1.1, U6.26 (IO4)
/BTN2: SW2.1, U6.16 (IO13)
/BTN3: SW3.1, U6.27 (IO16)
/BTN4: SW4.1, U6.12 (IO27)
/BTN5: D6.2 (A), U6.8 (IO32)
/BTN5_SW: D5.1 (K), D6.1 (K), SW5.1
/CC1: J1.A5 (CC1), R1.1
/CC2: J1.B5 (CC2), R2.1
/CELL_NEG: C7.2, J2.2, Q3.1, U4.6 (GND)
/CHG_LED_A: D3.2 (A), R25.2
/CHG_N: D3.1 (K), U3.7 (~CHRG)
/CHG_PROG: R7.1, U3.2 (PROG)
/DTR_N: Q2.2 (E), R22.1, U2.13 (~DTR)
/EN: C4.1, Q1.3 (C), R5.2, TP5.1, U6.3 (EN)
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
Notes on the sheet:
1–2 USB-C INPUT, CC SINK, AND ESD
3–4 CH340C USB-UART / AUTO PROGRAM
GPIO19/20 carry native USB D-/D+ through 22-ohm resistors. USB Serial/JTAG supports automatic download. VBUS is sensed through Q1 for self-powered USB-device firmware; this Type-C port remains a sink/device, not a host power source.
5 TP4056 CHARGER (~500 mA)
6 CELL PROTECTION (DW01A + FS8205A)
Overcurrent estimate: 150mV typical / (2×25mΩ) ≈3.0A at high gate; 150mV / (2×35mΩ) ≈2.14A at low gate. Tolerance/temp range is broader.
7–10 LOAD SHARE, PTC, SWITCH, 3.3 V BUCK-BOOST
USB present: D1 powers SYS_RAW and Q4 is off; TP4056 independently charges BAT_CELL. USB absent: Q4 body diode starts SYS_RAW then P-MOS turns on. Switch is downstream of charger. TPS63021 maintains 3.3V in buck/transition/boost; TI specifies 2A for VIN >2.5V. 2.2uH is sized for this <=1A rail.
11–12 ESP32-WROOM MODULE, ADC, AND SX1262 RADIO
BAT_SENSE uses ADC1 GPIO1; POT_ADC uses ADC1 GPIO2. 100k/100k gives 4.2V -> 2.1V; 21uA drain. Firmware: warn about 3.3V and orderly shutdown about 3.0-3.1V loaded; DW01 cutoff is backup only.
13–15 I2S MICROPHONE, CLASS-D AMP, SPEAKER
GAIN_SLOT tied directly to GND = +12dB. GPIO4 high enables left-channel audio; low shuts down. MAX98357A raw supply sees ≈3.0–4.2V battery or ≈4.7V from USB after SS34 (<5.5V max).
16 COMMERCIAL SSD1306 I2C OLED MODULE HEADER
Four through-hole connections only: pin 1 GND, pin 2 3V3, pin 3 SCL, pin 4 SDA. The commercial module supplies its own SSD1306 charge-pump parts; no raw SYS_SW reaches OLED logic.
17–20 POT, LED, 5× TWO-PIN BUTTONS, TEST PADS
Buttons: ESP32-S3 GPIO4/5/6/7/15 -> switch -> GND; firmware enables internal pull-ups. There are exactly 10 button holes, 3 pot holes, 2 LED holes, 4 OLED holes, and 2 power-switch holes.
SOFT POWER: hold BTN5 for 2 s. A press immediately wakes hardware; firmware must assert GPIO12/PWR_HOLD only after validating the full 2 s startup hold. While running, release PWR_HOLD after a 2 s shutdown hold; power drops when BTN5 is released. Typical OFF leakage target <2 uA; verify prototypes 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
